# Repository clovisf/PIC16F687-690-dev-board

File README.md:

# PIC16F687-690-dev-board

 A PIC16F690/685/687/689 based development board, featuring a connector for PICKIT3, a LED on PC0 and a 20 pin 1 row 2.54 connector for breadboard.

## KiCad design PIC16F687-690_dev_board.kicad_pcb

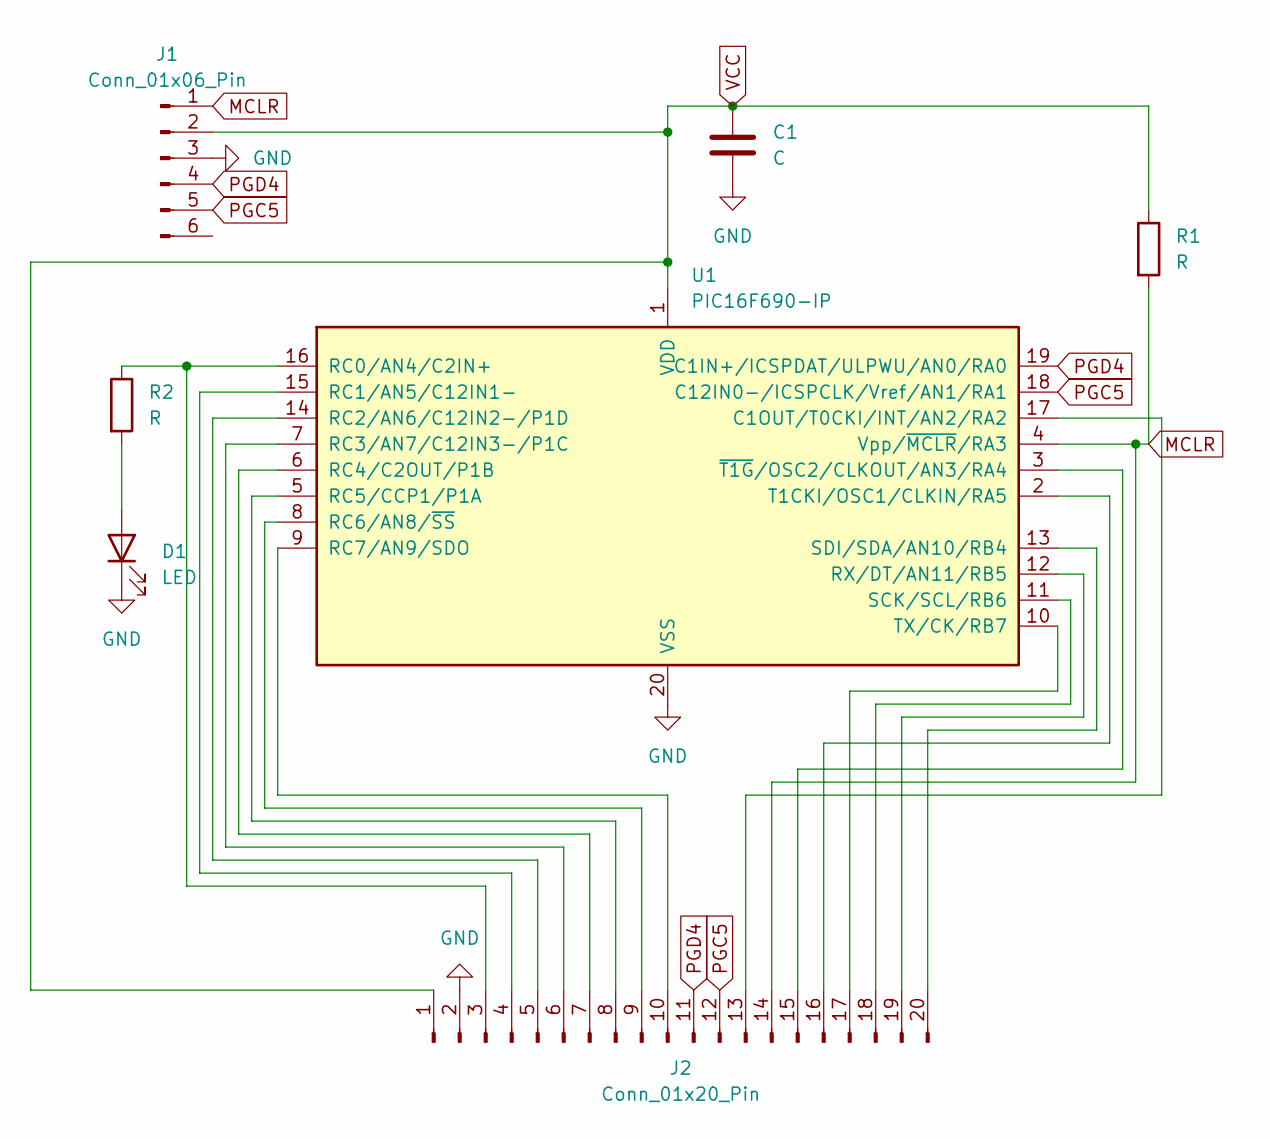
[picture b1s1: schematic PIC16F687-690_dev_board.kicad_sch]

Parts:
C1: C; C_Disc_D5.0mm_W2.5mm_P5.00mm
D1: LED; LED_D5.0mm
J1: Conn_01x06_Pin; PinHeader_1x06_P2.54mm_Horizontal
J2: Conn_01x20_Pin; PinHeader_1x20_P2.54mm_Vertical
R1, R2: R; R_Axial_DIN0411_L9.9mm_D3.6mm_P12.70mm_Horizontal
U1: PIC16F690-IP; DIP-20_W7.62mm

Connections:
GND: C1.2, D1.1 (K), J1.3, J2.2, U1.20 (VSS)
MCLR: J1.1, J2.14, R1.2, U1.4 (Vpp/~MCLR/RA3)
unnamed: D1.2 (A), R2.2
unnamed: J2.3, R2.1, U1.16 (RC0/AN4/C2IN+)
unnamed: J2.4, U1.15 (RC1/AN5/C12IN1-)
unnamed: J2.5, U1.14 (RC2/AN6/C12IN2-/P1D)
unnamed: J2.6, U1.7 (RC3/AN7/C12IN3-/P1C)
unnamed: J2.7, U1.6 (RC4/C2OUT/P1B)
unnamed: J2.8, U1.5 (RC5/CCP1/P1A)
unnamed: J2.9, U1.8 (RC6/AN8/~SS)
unnamed: J2.10, U1.9 (RC7/AN9/SDO)
unnamed: J2.13, U1.17 (C1OUT/T0CKI/INT/AN2/RA2)
unnamed: J2.15, U1.3 (~T1G/OSC2/CLKOUT/AN3/RA4)
unnamed: J2.16, U1.2 (T1CKI/OSC1/CLKIN/RA5)
unnamed: J2.17, U1.10 (TX/CK/RB7)
unnamed: J2.18, U1.11 (SCK/SCL/RB6)
unnamed: J2.19, U1.12 (RX/DT/AN11/RB5)
unnamed: J2.20, U1.13 (SDI/SDA/AN10/RB4)
PGC5: J1.5, J2.12, U1.18 (C12IN0-/ICSPCLK/Vref/AN1/RA1)
PGD4: J1.4, J2.11, U1.19 (C1IN+/ICSPDAT/ULPWU/AN0/RA0)
VCC: C1.1, J1.2, J2.1, R1.1, U1.1 (VDD)

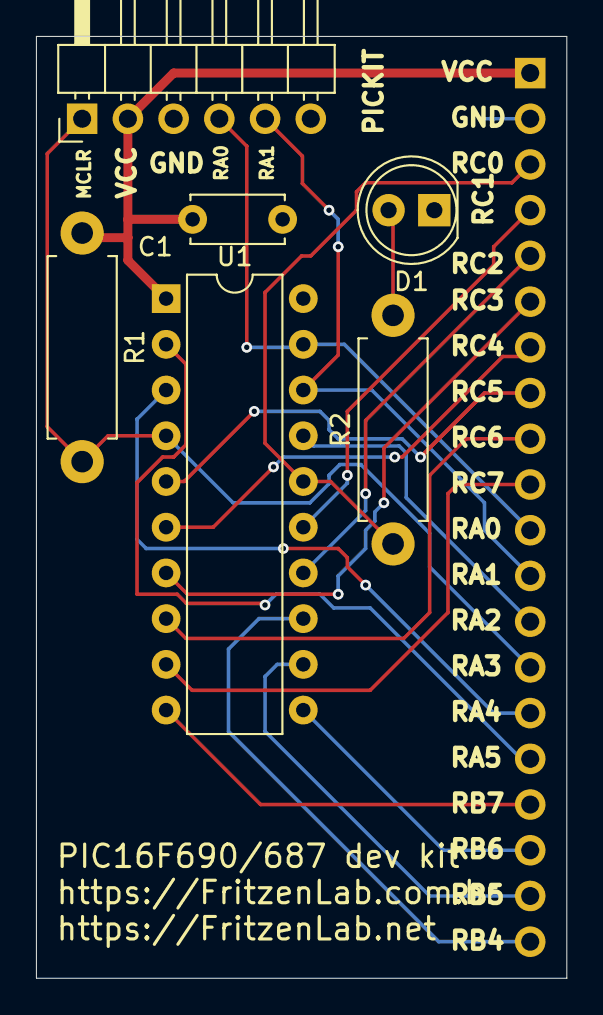
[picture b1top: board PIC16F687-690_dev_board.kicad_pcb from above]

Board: 2 copper layers, 29.5 x 52.3 mm, 7 parts (1 on the bottom side), 21 nets.

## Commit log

2024-05-10 First commit - PIC dev board
    First commit - PIC dev board
2024-05-12 finalized layout organization
    finalized layout organization
2024-05-12 finished silkscreen
    finished silkscreen and sent into production at JLCPCB
2024-05-15 gerber files upload
    gerber files upload
2024-10-21 backups
